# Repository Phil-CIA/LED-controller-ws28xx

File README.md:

# My LED Controller

Standalone ESP32 + WS281x project.

This repo now supports two firmware paths:
- custom firmware in `src/main.cpp` (serial-driven tests and demo)
- official WLED firmware (Wi-Fi + WLED app control)

This repo now also supports two hardware targets:
- `breadboard` target profile
- `pcb` target profile

Each target has independent identity lock (port/chip/MAC) in `scripts/flash-targets.json`.

## Hardware
- MCU: ESP32 family (default board config: esp32dev)
- LED data: GPIO18
- LED type: WS281x (NEO_GRB + 800kHz)
- LED count: 300
- Level shifter: 74H125
- Upload port: COM5

## Quick start
1. Set active target profile
   - Breadboard: `powershell -ExecutionPolicy Bypass -File scripts/set-active-target.ps1 -TargetName breadboard`
   - PCB: `powershell -ExecutionPolicy Bypass -File scripts/set-active-target.ps1 -TargetName pcb`
2. Build custom firmware for selected target
   - `powershell -ExecutionPolicy Bypass -File scripts/guarded-flash.ps1 -Action build`
3. Upload custom firmware for selected target (guarded)
   - `powershell -ExecutionPolicy Bypass -File scripts/guarded-flash.ps1 -Action upload`
4. Monitor
   - `platformio device monitor -b 115200 -p COM5`

## Target profile setup
Before first guarded flash on a target, pin its immutable MAC:
- `powershell -ExecutionPolicy Bypass -File scripts/set-target-mac.ps1 -TargetName pcb -ExpectedMac 11:22:33:44:55:66`

If `expectedMac` is empty for a target, guarded upload refuses to flash.

## WLED quick start (Wi-Fi + app)
1. Set active target profile first (`breadboard` or `pcb`).
2. Use the official installer at `https://install.wled.me` (ESP32 target).
3. Select the target COM port and complete flashing through the installer UI.
4. On first boot, connect to the WLED access point (`WLED-xxxxxx`) and open `http://4.3.2.1`.
5. In WLED settings, set hardware values to match this strip:
   - GPIO: `18`
   - LED count: `300`
   - Color order: `GRB`
6. Configure home Wi-Fi credentials in WLED settings and save.
7. Open the WLED app and add the device using `wled.local` or the assigned IP.
8. Set WLED max current to `12000 mA` for steady-state operation.
9. Discover by target profile:
   - Breadboard: `powershell -ExecutionPolicy Bypass -File scripts/discover-wled.ps1 -TargetName breadboard -OpenUi`
   - PCB: `powershell -ExecutionPolicy Bypass -File scripts/discover-wled.ps1 -TargetName pcb -OpenUi`

### If device reboots with `invalid header`
- This indicates an incompatible direct flash layout.
- Recover to known-good firmware with guarded upload:
  - `powershell -ExecutionPolicy Bypass -File scripts/guarded-flash.ps1 -Action upload`
- Then use `install.wled.me` instead of raw one-file `esptool write-flash` for WLED.

## Serial commands
- `on` => resume animation
- `off` => LEDs off
- `rainbow` => return to rainbow mode
- `white`, `red`, `green`, `blue` => solid color test
- `probe` => raw GPIO18 pulse test
- `b0` to `b255` => set brightness

## Rev B action list (from validated PCB bring-up)
- Keep LED outputs as validated:
   - external strip data on `GPIO18`
   - onboard 3-LED chain on `GPIO19`
- Keep sensor wiring as validated:
   - AHT20 `SDA=GPIO21`, `SCL=GPIO22`
   - I2C address detected at `0x38`
- Fix switch hardware biasing on PCB:
   - Current switch pins (`GPIO34`, `GPIO35`, `GPIO36`, `GPIO39`) have no internal pull-up/down support.
   - Add external pull resistors per switch (recommended: `10k` pull-up to `3.3V`, button to `GND`, active-low).
- Preserve guarded flash identity lock per target in `scripts/flash-targets.json`.
- Keep target-separated profiles (`breadboard`, `pcb`) and avoid MAC reuse across targets.

## PCB diagnostics commands
- `aht20` or `sensor` => read temperature/humidity from AHT20
- `i2cscan` or `scan` => scan bus and print detected I2C addresses
- `switches` or `inputs` => print raw switch pin states
- `boardcheck` or `diag` => run sensor + switches diagnostics together

## Notes
- If your exact ESP32 board is different, update `board` in platformio.ini.
- If colors are wrong, adjust pixel order in src/main.cpp.
- Keep strict target guardrails in place; do not flash unknown devices opportunistically.
- Use dedicated VS Code tasks per target (`Breadboard:*` and `PCB:*`).

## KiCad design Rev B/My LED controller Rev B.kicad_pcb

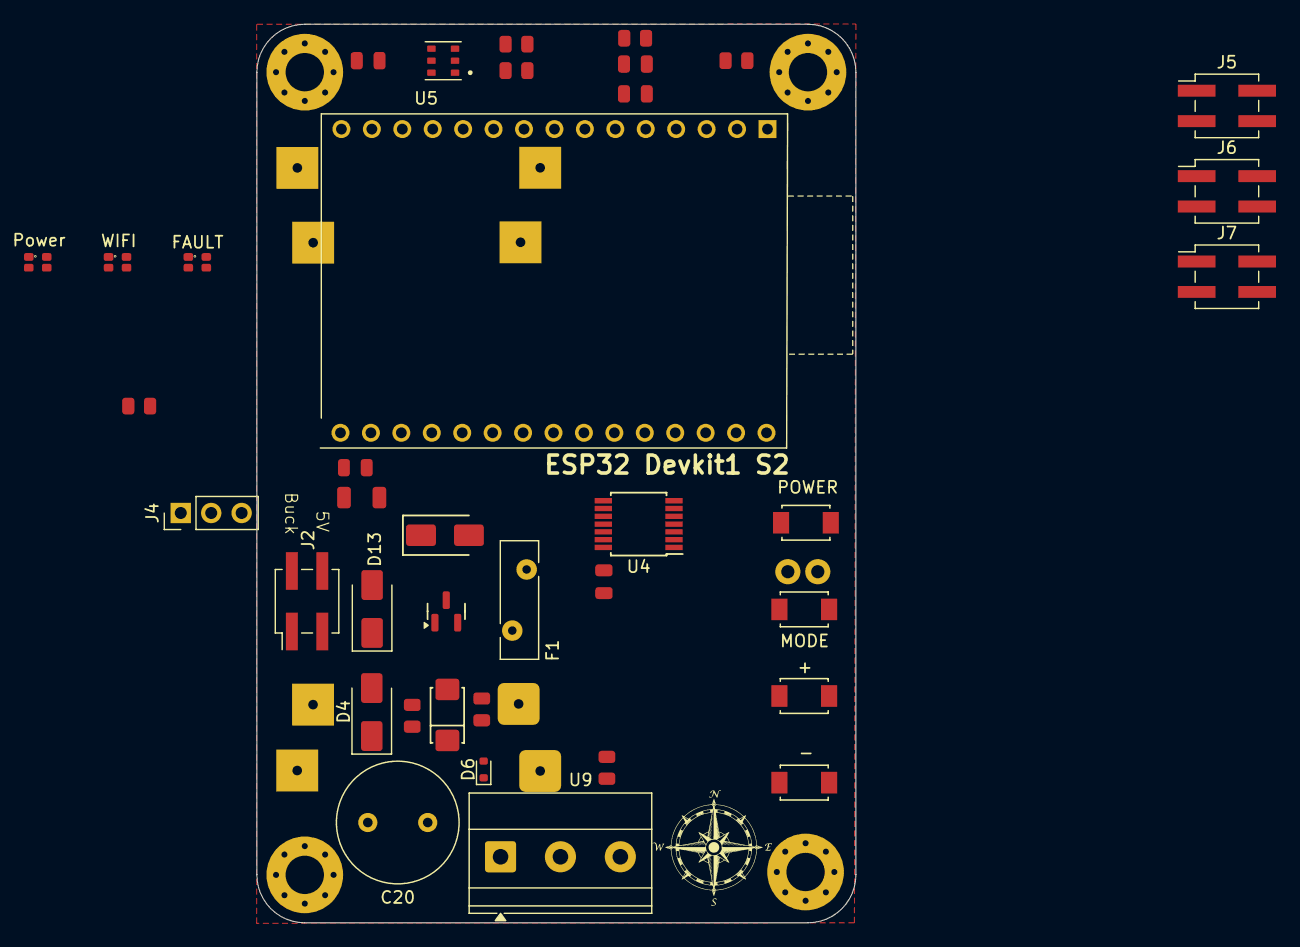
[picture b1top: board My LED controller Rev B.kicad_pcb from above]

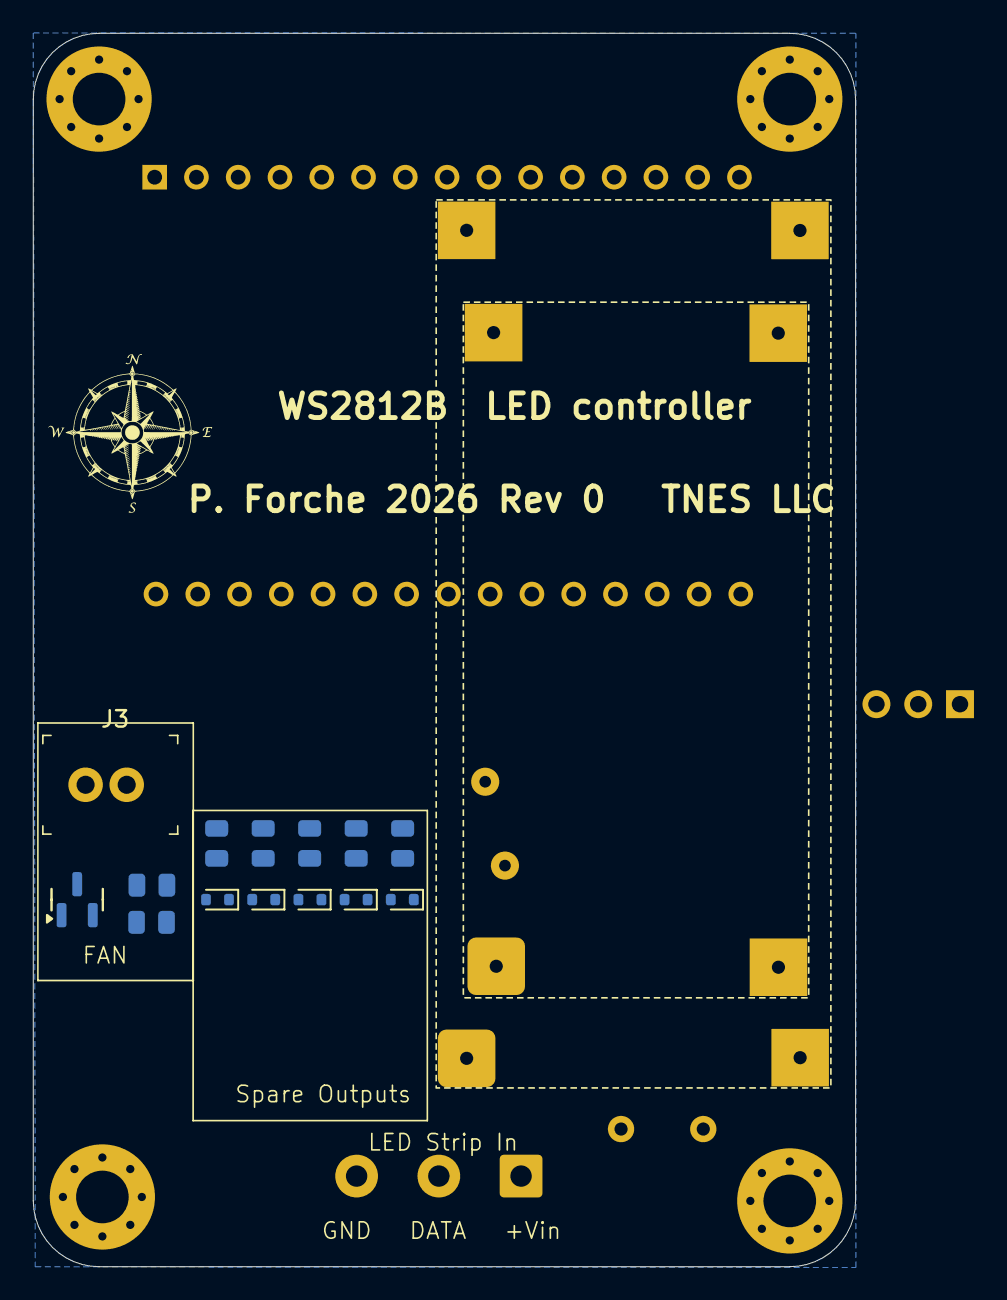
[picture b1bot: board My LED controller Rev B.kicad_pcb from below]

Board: 2 copper layers, 50.0 x 75.0 mm, 59 parts (16 on the bottom side), 39 nets, no tracks yet.

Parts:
10mm1, 10mm2: 10mm LOGO
BUCK1: Amazon Buck FP
C1, C3, C19: 100nF; C_0805
C2: 100uF; C_1206
C17: 10uF; C_0805
C18: 0.1uF; C_0805
C20: 1000uF; C_Radial_D10.0mm_H12.5mm_P5.00mm
D1, D2, D3: WS2812B; LED-SMD_4P-L1.6-W1.5_XL-1615RGBC-WS2812B
D4: SMAJ26CA; D_SMA
D5: SMAJ5.0CA; D_SMA
D6, D7, D8, D9, D10, D11: ESD5Z5.0T1G; D_SOD-523
D12: 1SMA5927A; D_DO-214AC(SMA)
D13: US1M; D_SMA
F1: PTC RESET FUSE 700mA TH; Fuse_Bourns_MF-RHT100
H1, H2, H3, H4: MHolePad; MountingHole_3.2mm_M3_Pad_Via
J2: Power SEL; PinHeader_2x02_P2.54mm_Vertical_SMD
J3: Fan Control; PinHeader_1x2_P2.5mm_Drill1.1mm
J4: Conn_01x03_Pin; PinHeader_1x03_P2.54mm_Vertical
J5, J6, J7: SPARE_OUT_HDR; PinHeader_2x02_P2.54mm_Vertical_SMD
Q1: BSP322; Q_SOT-23
Q2: AO3400A; Q_SOT-23
R1, R5: 10kΩ; R_0805
R2, R3, R4, R7, R8, R9, R15, R16: 100Ω; R_0805
R6, R10: 100kΩ; R_0805
R12, R13: 4.7k; R_0805
R14: 220Ω; R_0805
SW3: -; SW_TS-1088-AR02016
SW4: +; SW_TS-1088-AR02016
SW5: MODE; SW_TS-1088-AR02016
SW6: POWER; SW_TS-1088-AR02016
U1: ESP32-DevKitM-1; ESP32-C3-DevKitM-1
U4: SN74AHCT125PWR; TSSOP-14_4.4x5mm_P0.65mm
U5: AHT20_C2757850; Humidity sensor
U9: LED_STRIP_CONN; TerminalBlock_Phoenix_MKDS-1,5-3_1x03_P5.00mm_Horizontal

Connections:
3Y: J4.2, R3.1, U4.8 (3Y)
4Y: J5.2, R2.1, U4.11 (4Y)
+3.3V: C2.1, C3.1, R1.1, R12.1, R13.1, R14.1, U1.16 (VDD_3V3)
+5V_CTRL: BUCK1.4 (+Vout), C1.1, C19.2, D1.2 (VDD), D2.2 (VDD), D3.2 (VDD), D5.2, J2.4, J4.3, J5.3, J6.3, U1.15 (Vin), U4.14 (VCC)
GND: BUCK1.1 (-Vin), BUCK1.3 (-Vout), C1.2, C2.2, C3.2, C17.2, C18.2, C19.1, C20.2, D1.3 (GND), D2.3 (GND), D3.3 (GND), D4.1 (A1), D5.1, D6.2 (A), D7.2 (A), D8.2 (A), D9.2 (A), D10.2 (A), D11.2 (A), H1.1, H2.1, H3.1, H4.1, J4.1, J5.1, J6.1, Q2.2 (S), R6.2, R10.2, SW3.2, SW4.2, SW5.2, SW6.2, U1.14 (GND), U1.17 (GND), U4.1 (~1OE), U4.4 (~2OE), U4.7 (GND), U4.10 (~3OE), U4.13 (~4OE), U5.5 (GND), U9.3
GPIO12: R16.2, U1.12 (GPIO12)
GPIO13: J7.2, R8.1, U1.13 (GPIO13)
GPIO14: J7.1, R7.1, U1.11 (GPIO14)
GPIO16: U1.21 (GPIO16), U4.2 (1A)
GPIO17: U1.22 (GPIO17), U4.5 (2A)
GPIO18: U1.24 (GPIO18), U4.12 (4A)
GPIO19: U1.25 (GPIO19), U4.9 (3A)
GPIO23: R9.1, U1.30 (GPIO23)
GPIO34: SW3.1, U1.4 (GPIO34)
GPIO35: SW4.1, U1.5 (GPIO35)
GPIO36: SW5.1, U1.2 (GPIO36)
GPIO39: SW6.1, U1.3 (GPIO39)
LED_STRIP: R15.1, U4.3 (1Y)
unnamed: BUCK1.2 (+Vin), J2.2
unnamed: D1.4 (DIN), R16.1
unnamed: D1.1 (DOUT), D2.4 (DIN)
unnamed: D2.1 (DOUT), D3.4 (DIN)
unnamed: D6.1 (K), R15.2, U9.2
unnamed: D7.1 (K), R4.2
unnamed: D8.1 (K), R3.2
unnamed: D9.1 (K), R2.2
unnamed: D10.1 (K), R8.2
unnamed: D11.1 (K), R7.2
unnamed: D13.2 (A), J3.1, Q2.3 (D)
unnamed: D12.1, Q1.1 (G), R5.2, R6.1
unnamed: Q2.1 (G), R9.2, R10.1
unnamed: R1.2, U1.1 (EN_/_RESET)
unnamed: C17.1, C18.1, R14.2, U5.2 (VDD)
SCL: R12.2, U1.29 (I2C-SCL), U5.3 (SCL)
SDA: R13.2, U1.26 (I2C_SDA), U5.4 (SDA)
VIN_CLAMPED: D4.2 (A2), D13.1 (K), F1.2, J2.1, J2.3, J3.2
VIN_RAW: C20.1, Q1.2 (D), R5.1, U9.1
VIN_REVPROT: D12.2, F1.1, Q1.3 (S)
Y2: J6.2, R4.1, U4.6 (2Y)

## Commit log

2026-06-02 Add files via upload
    netlist
2026-06-22 Swap Q1 gate bias resistors: R5 100k (to VIN_RAW), R6 10k (to GND) for better PMOS turn-on at 5V input
2026-06-22 Add handoff document for board connection & validation phase
2026-06-24 Implement pin remap docs and add spare AHCT125 SMT breakout header
2026-06-24 Schematic: mirror WS2812 symbols and adjust annotation placement
2026-06-24 Add living Rev B change tracker and link quickstart
2026-06-29 Close session: update handoff with sync and Rev B tracker status
2026-06-29 Add Rev B design baseline and prefab mic closeout artifacts
2026-06-29 Close session and publish Rev B pre-route kickoff plan
